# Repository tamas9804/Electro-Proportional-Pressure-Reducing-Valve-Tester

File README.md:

# Elektronikus nyomáscsökkentő szelep tesztelő

## Megvalósítandó funkciók

### 1. Mérési funkciók 
* **Szelepek folytonosságának mérése:** Gyors szakadás- és zárlatvizsgálat a szelepek tekercsén.
* **Nagy pontosságú ellenállásmérés:** A szelepek tekercsellenállásának precíziós mérése **0,1%-os pontossággal**, ami lehetővé teszi a minimális menetzárlatok vagy degradációk kiszűrését is.
* **Többcsatornás architektúra:** A rendszernek alkalmasnak kell lennie egyszerre két szelep fogadására és mérésére/tesztelésére.

### 2. Vezérlési és hajtás funkciók 
* **Teljes kivezérlés:** A szelepek direkt, folyamatos (100%-os) kivezérlése a maximális elmozdulás és működés ellenőrzéséhez.
* **PWM kivezérlés:** Impulzusszélesség-modulált (PWM) jel biztosítása a proporcionális szelepek áram- és nyomásszabályzási karakterisztikájának teszteléséhez.
* **Polaritásváltás (H-híd konfiguráció):** A hardvernek felkészültnek kell lennie a polaritás szoftveres felcserélésére, biztosítva a jövőbeli kompatibilitást a többállású vagy irányváltó szelepekkel.

### 3. Hardver és elektromos védelem 
* **Széles tápfeszültség-tartomány:** Az áramkörnek stabilan kell üzemelnie **12V és 24V DC** közötti betáplálási feszültségen, alkalmazkodva az ipari és járműipari szabványokhoz.
* **Fordított polaritás elleni védelem:** Védelem a tápvezetékek téves felcserélése ellen a belső elektronika megóvása érdekében.
* **Túláramvédelem:** A fő tápágat egy **10A-es biztosíték** védi a zárlatokból vagy túlterhelésekből adódó károk ellen.

### 4. Felhasználói felület és szoftver 
* **Beépített menürendszer:** A műszernek rendelkeznie kell egy lokális kijelzőn és fizikai nyomógombokon keresztül kezelhető, jól strukturált menürendszerrel. A szoftvernek kötelezően biztosítania kell az alábbi dedikált menüpontokat:
  * **Teljes teszt:** Egy automatizált tesztszekvencia, amely felhasználói beavatkozás nélkül, egymás után elvégzi a szakadásvizsgálatot, az ellenállásmérést, és végül teljesen kivezérli a szelepet.
  * **Szakadásvizsgálat:** Külön menüpont a tekercs folytonosságának gyors és célzott ellenőrzésére.
  * **Ellenállásmérés:** Dedikált funkció a szelep tekercsellenállásának precíziós mérésére.
  * **Teljes kivezérlés:** A szelep 100%-os, folyamatos statikus meghajtása az azonnali működés-ellenőrzéshez.
  * **PWM kivezérlés:** Impulzusszélesség-modulált (PWM) jel kiadása a szelep proporcionális mozgásának teszteléséhez.
  * **Beállítások:** Rendszerkonfigurációs menü, ahol a felhasználó megadhatja a tesztelt szelepek számát, illetve kiválaszthatja a kívánt nyelvet.
* **Többnyelvűség:** A szoftver képesnek kell lennie több nyelv (Magyar, Angol, Német) dinamikus kezelésére és tartós tárolására.A műszernek újraindítás után is megkell jegyeznie az elmentett szelepek számát, illetve a beállított nyelvet

##  Kiválasztott hardverkomponensek 

A projekt áramköri kialakítása során a fő szempont a megbízhatóság, a költséghatékonyság, valamint az ipari (12-24V) környezetnek való megfelelés volt. Az áramkör az alábbi főbb alkatrészekre épül:

### 1 Vezérlés és Megjelenítés
* **Arduino Nano (ATmega328P):** Költséghatékony, könnyen programozható, és az I/O lábszáma, valamint a számítási kapacitása tökéletesen elegendő a műszer funkcióinak (állapotgép, I2C kommunikáció, PWM) ellátására.
* **16x4 LCD kijelző (I2C modullal):** A teszteredmények és a menürendszer megjelenítéséért felel. Az I2C bővítőnek köszönhetően mindössze két adatvonalat (SDA, SCL) igényel, így rengeteg portot spórol meg a mikrokontrolleren, és a programozása is rendkívül egyszerű.
### 2 Precíziós Mérésadatgyűjtés
* **ADS1115 (16-bites ADC):** A mikrokontroller beépített, alacsonyabb felbontású analóg-digitális átalakítója helyett ez a dedikált IC garantálja a rendkívül pontos (akár 0,1%-os) áram- és feszültségmérést.
* **LM317 feszültségszabályzó (Áramgenerátoros módban):** A precíziós ellenállásmérés alapja. Stabil, állandó mérőáramot biztosít a szelepek tekercsére, ami elengedhetetlen a pontos ellenállás kiszámításához.
* **Feszültségosztó hálózat:** Egy dedikált, egyszerű és gyors mérőáramkör a tekercsek folytonosságának azonnali ellenőrzésére.
### 3. Teljesítményvezérlés és Tápellátás
* **LM2596S DC-DC Step-down konverter:** A műszer tápegysége. A széles ipari feszültségtartományt (12V - 24V) hatékonyan és biztonságosan alakítja át a logikai áramkörök számára szükséges 5V-os stabil feszültségre.
* **AOD409 (P-csat) és IRLR2705 (N-csat) MOSFET-ek:** Ezek a nagy áramtűrésű tranzisztorok felelnek a szelepek (H-híd topológiájú) meghajtásáért. Biztosítják a biztonságos, melegedésmentes PWM szabályozást és a folyamatos, 100%-os kivezérlést a legnagyobb áramfelvételű szelepek esetén is.
* **SRD-05VDC-SL-C 5V Relék:** Mechanikus kapcsolóelemek, amelyek a különböző mérési körök (pl. áramgenerátoros mérés és PWM hajtás) fizikai és galvanikus leválasztását végzik, védve ezzel az érzékeny mérőelektronikát a tesztelés során.
### 4. Mechanika és Csatlakozók
* **JST XH csatlakozók a PCB-n:** A kijelző, a nyomógombok és a potenciométerek nem közvetlenül a panelre vannak forrasztva, hanem szabványos XH csatlakozókkal csatlakoznak. Ez drasztikusan megkönnyíti az alkatrészek cseréjét, valamint sokkal nagyobb szabadságot ad a végleges műszerház (enclosure) 3D tervezésénél és összeszerelésénél

## Részletes Áramköri Felépítés

Mivel a teljes kapcsolási rajz A3-as méretű, a könnyebb átláthatóság és olvashatóság érdekében funkcionális blokkokra bontva mutatjuk be a hardver működését.

A teljes rajz letölthető [**PDF formátumban**](Hardware/EPPR_tester_full.pdf)

### 1. Tápellátás és Fordított Polaritás Elleni Védelem
Ez a modul felel a rendszer stabil feszültségellátásáért. A 24V-os bemenetet egy biztosíték és egy dióda védi a fordított polaritás ellen. Egy **LM2596S** kapcsolóüzemű szabályzó állítja elő a logikai áramkörök számára szükséges stabil 5V-ot nagy hatásfokkal.

### 2. Vezérlő interfészek és Felhasználói Felület csatlakozók
Itt látható az **Arduino Nano** mikrokontroller központi bekötése. Ez a modul kezeli az I2C buszt az LCD kijelzőt és az ADC-t. Tartalmazza a JST XH csatlakozók bekötését a navigációs nyomógombokhoz, a potméterhez.

#### 3. Precíziós Analóg-Digitális Átalakítás 
A nagy pontosságú mérésekért egy **ADS1115** 16-bites külső ADC modul felel. I2C buszon kommunikál a vezérlővel.

### 4 Polaritás váltó híd 
Ez az áramkör tartalmazza a polaritás váltást az adott kimeneten, illetve kezeli hogy 12V illetve 24V-ről is tudjon működni.

### 5 Mérési Mód Választó Relé 
Ez a modul választja ki, hogy az ADC éppen az analóg mérőjelet vagy a folytonossági teszthez szükséges feszültségosztót olvassa be.

### 6 Szelep Szekvencia Választó Relék
Ez a rész kapcsolja a kimenetet, ezzel a kapcsolással egyszerre két szelep is rácsatlakoztatható és külön külön lemérhető.

### 7 Szelep Csatlakozók és Állapotjelző LED-ek
Ez a kimeneti modul tartalmazza a fizikai sorkapcsokat a szelepek bekötéséhez. Tartalmazza az optikai visszajelzést biztosító LED csatlakozását amelyek mutatják az adott szelep kimenet állapotát.

## Nyomtatott Áramkör 

A megbízható és zajmentes ipari működés érdekében a NYÁK-tervezés során az alábbi tervezési irányelveket követtem:

* **4 rétegű felépítés:** A panel ipari szabványú **FR-4**-es hordozóanyagra készült, 4 rétegű kialakítással. Ez lehetővé tette a jelvezetékek és a tápvezetékek optimális szétválasztását.
* **Dedikált Föld és Táp síkok:** A kiváló zajvédelem érdekében a két belső réteg dedikált feladatot kapott. Az egyik egy megszakítás nélküli, masszív Föld-sík, a másik pedig egy egybefüggő Táp-sík (5V). Ez minimalizálja a hurok-induktivitást és stabil referenciát biztosít a precíziós analóg mérésekhez.
* **Áramra méretezett vezetősávok:** A teljesítményelektronikai részeknél a vezetősávok szélessége a maximális átfolyó áramra lett méretezve a melegedés és a feszültségesés elkerülése végett.
* **Zajszűrés optimalizálása:** A tápszűrő kondenzátorok fizikailag a lehető legközelebb kerültek az integrált áramkörök (Arduino Nano, ADS1115, LM317) táplábaihoz, így hatékonyan nyelik el a magas frekvenciás tranzienseket.
* **Adatvonalak árnyékolása:** A kritikus kommunikációs vonalak (például az I2C busz SDA és SCL vonalai) a rézrétegen mindkét oldalról föld-sávokkal lettek körbevéve. Ez a technika drasztikusan csökkenti az áthallást és megvédi az érzékeny digitális jeleket a relék által keltett zavaroktól.
* **Precíziós Analóg Tápszűrés:** Az **ADS1115** 16-bites ADC tápellátását egy dedikált ferrit szűrővel választottuk le a közös 5V-os digitális tápvezetékről. Ez a szűrőmegoldás hatékonyan blokkolja a mikrokontroller és a digitális kapcsolóelemek által keltett nagyfrekvenciás zajokat, így garantálja a zajmentes tápfeszültséget az ADC számára, ami elengedhetetlen a 0,1%-os mérési pontosság eléréséhez.

## 3D Modell

A nyomtatott áramkörről és a rászerelt alkatrészekről egy teljes 3D modell készült. Ez a modell alapvető fontosságú a műszer külső dobozolásának megtervezéséhez, az ütközések ellenőrzéséhez, valamint a gombok és a kijelző pontos pozicionálásához.

**A PCB 3D-s látványterve :**
[**Kattints ide a panel interaktív 3D megtekintéséhez!**](Hardware/3D%20file/EPPR%20tester.stl)

## Fizikai Összeépítés és Prototípus

Az alábbi képen a már legyártott, 4 rétegű **FR-4**-es nyomtatott áramkör látható a valóságban, készre szerelt állapotban. 

**A kész, működőképes áramkör a valóságban:**

## Szoftver Architektúra és Kódolási Irányelvek 

A beágyazott szoftver **C++ nyelven**, az Arduino keretrendszerre támaszkodva íródott. A kódolás során a fő szempont a megbízhatóság, a mikrokontroller szűkös erőforrásainak optimalizálása, valamint a méréstechnikai pontosság maximalizálása volt.

A fejlesztés során az alábbi kulcsfontosságú programozási technikákat alkalmaztuk:

### 1. Véges Állapotgép 
A szoftver működése egy robusztus, többszintű állapotgépre épül. Az állapotokat (Főmenü, Beállítások, Tesztelési folyamatok) `enum class` struktúrák vezérlik (`SystemMode`, `MenuStates`, `SettingStates`).
* **Előny:** Ez a megközelítés teljesen kiküszöböli az átláthatatlan kódot, és a `loop()` függvényt könnyen bővíthetővé teszi, elkerülve a blokkoló várakozásokat.

### 2. Memóriaoptimalizálás és Többnyelvűség
A műszer három nyelvet támogat (Magyar, Angol, Német). Mivel a kijelzőn megjelenő stringek gyorsan kimerítenék az Arduino Nano (ATmega328P) mindössze 2 kByte-os SRAM memóriáját, az összes szöveges konstans a **Flash memóriában (`PROGMEM`)** kapott helyet.
* **Megvalósítás:** Egy dedikált lekérdező függvény (`getText()`) olvassa ki a kért nyelvi elemeket futásidőben a Flash memóriából egy rövid bufferbe, drasztikusan csökkentve a futásidejű memóriafoglalást.

#### 3. Szoftveres Zajszűrés és Dinamikus Felbontás
A 0,1%-os pontosságú mérés érdekében a hardveres szűrés mellett speciális szoftveres eljárásokat is bevezettem:
* **Túlmintavételezés:** Az analóg értékek beolvasásakor a kód ciklusonként 100 mintát vesz, és ezek átlagolásával (`getAveragedVoltage()`) szűri ki a hálózati és kapcsolási zajokat.
* **Dinamikus Erősítés:** Az ellenállásmérés (`OhmTest`) során a szoftver az ADS1115-ös IC beépített programozható erősítőjét (PGA) dinamikusan állítja (`GAIN_EIGHT`, `GAIN_FOUR`, stb.). Ha a mért feszültség túl alacsony, a rendszer automatikusan nagyobb erősítésre kapcsol, így mindig kihasználja a 16-bites felbontás maximumát a különböző ellenállás-tartományokban.

#### 4. EEPROM Kezelés és "First Start" Detektálás
A felhasználói beállítások (kiválasztott nyelv, szelepek száma) a nem felejtő **EEPROM** memóriában tárolódnak.
* **Intelligens inicializálás:** A szoftver tartalmaz egy `doFirstStart()` logikát, amely egy specifikus azonosító (Magic Number: `78`) keresésével megállapítja, hogy a mikrokontroller most lett-e először felprogramozva. Ha igen, automatikusan feltölti az EEPROM-ot az alapértelmezett gyári értékekkel, megelőzve a memóriaszemétből adódó összeomlásokat.

#### 5. Hardveres Védelem és Tiszta Újraindítás
* A tesztelési fázisok indításakor és leállításakor a szoftver szigorú sorrendben kapcsolja a hardveres reléket és a PWM jeleket, hogy elkerülje a mérőáramkör túlterhelését.
* A beállítások mentése után a rendszer nem szoftveres trükkökkel, hanem a hardveres **Watchdog Timer (`wdt_enable`)** szándékos lejáratásával (`softwareReset()`) hajt végre egy teljesen tiszta újraindítást, garantálva, hogy minden regiszter és memóriacím az alapállapotba kerüljön.

## Javítási és Továbbfejlesztési Tervek 

Bár a műszer prototípusa teljesen működőképes és ellátja az alapvető mérési funkciókat, a jövőbeli verziókhoz az alábbi javítások lehetőségesek:

### Szoftveres javítások és optimalizálás (Known Issues & Fixes)
* **PWM Teszt implementálása:** A menürendszerben már szerepel, de a `PwmTest()` funkció logikája (a hardveres időzítők és a kitöltési tényező dinamikus állítása) még megírásra vár.
* **Blokkoló kódok kiváltása:** A tesztelési folyamatok végén jelenleg `delay(4000)` található. Ezt a jövőben `millis()` alapú, nem blokkoló időzítésre cseréljük, hogy a műszer közben reagálhasson a gombnyomásokra.
* **Kalibrációs menü:** Egy rejtett menüpont létrehozása, ahol az áramgenerátor és a feszültségosztó pontatlanságait szoftveresen (Offset és Gain értékekkel) lehet kalibrálni és az EEPROM-ba menteni.

### Hardveres és Rendszerszintű továbbfejlesztések
* **Induktív visszarúgás elleni védelem:** A jelenlegi V1.0-s nyomtatott áramkörről lemaradtak a szelepek (induktív terhelések) kikapcsolásakor keletkező feszültségtüskék elleni védődiódák. A működő prototípuson ezt ideiglenesen utólagos ráforrasztással oldottuk meg. A következő PCB terv frissítésnél ezek a Schottky védődiódák dedikált helyet és megfelelő hűtőfelületet kapnak a H-híd kimeneteinél, garantálva a MOSFET-ek hosszú távú védelmét.
* **Adatnaplózás (Data Logging):** Egy MicroSD kártya modul integrálása az I2C/SPI buszra, hogy a teszteredményeket .CSV formátumban el lehessen menteni a későbbi elemzéshez.
* **PC-s kommunikáció (Serial Plotter):** A tesztelés alatti áram- és feszültséggörbék (különösen a PWM kivezérlés esetén) folyamatos küldése USB-n keresztül egy PC-s szoftvernek, vizuális grafikonrajzolás céljából.

### Karbantartás és Fizikai javítás 
A hardver úgy lett megtervezve, hogy a terepi javítás a lehető legegyszerűbb legyen:
* **Relék és Csatlakozók:** A mechanikus kopásnak kitett alkatrészek (SRD relék), egy esetleges beégés esetén könnyen kicseréhetővé tétele

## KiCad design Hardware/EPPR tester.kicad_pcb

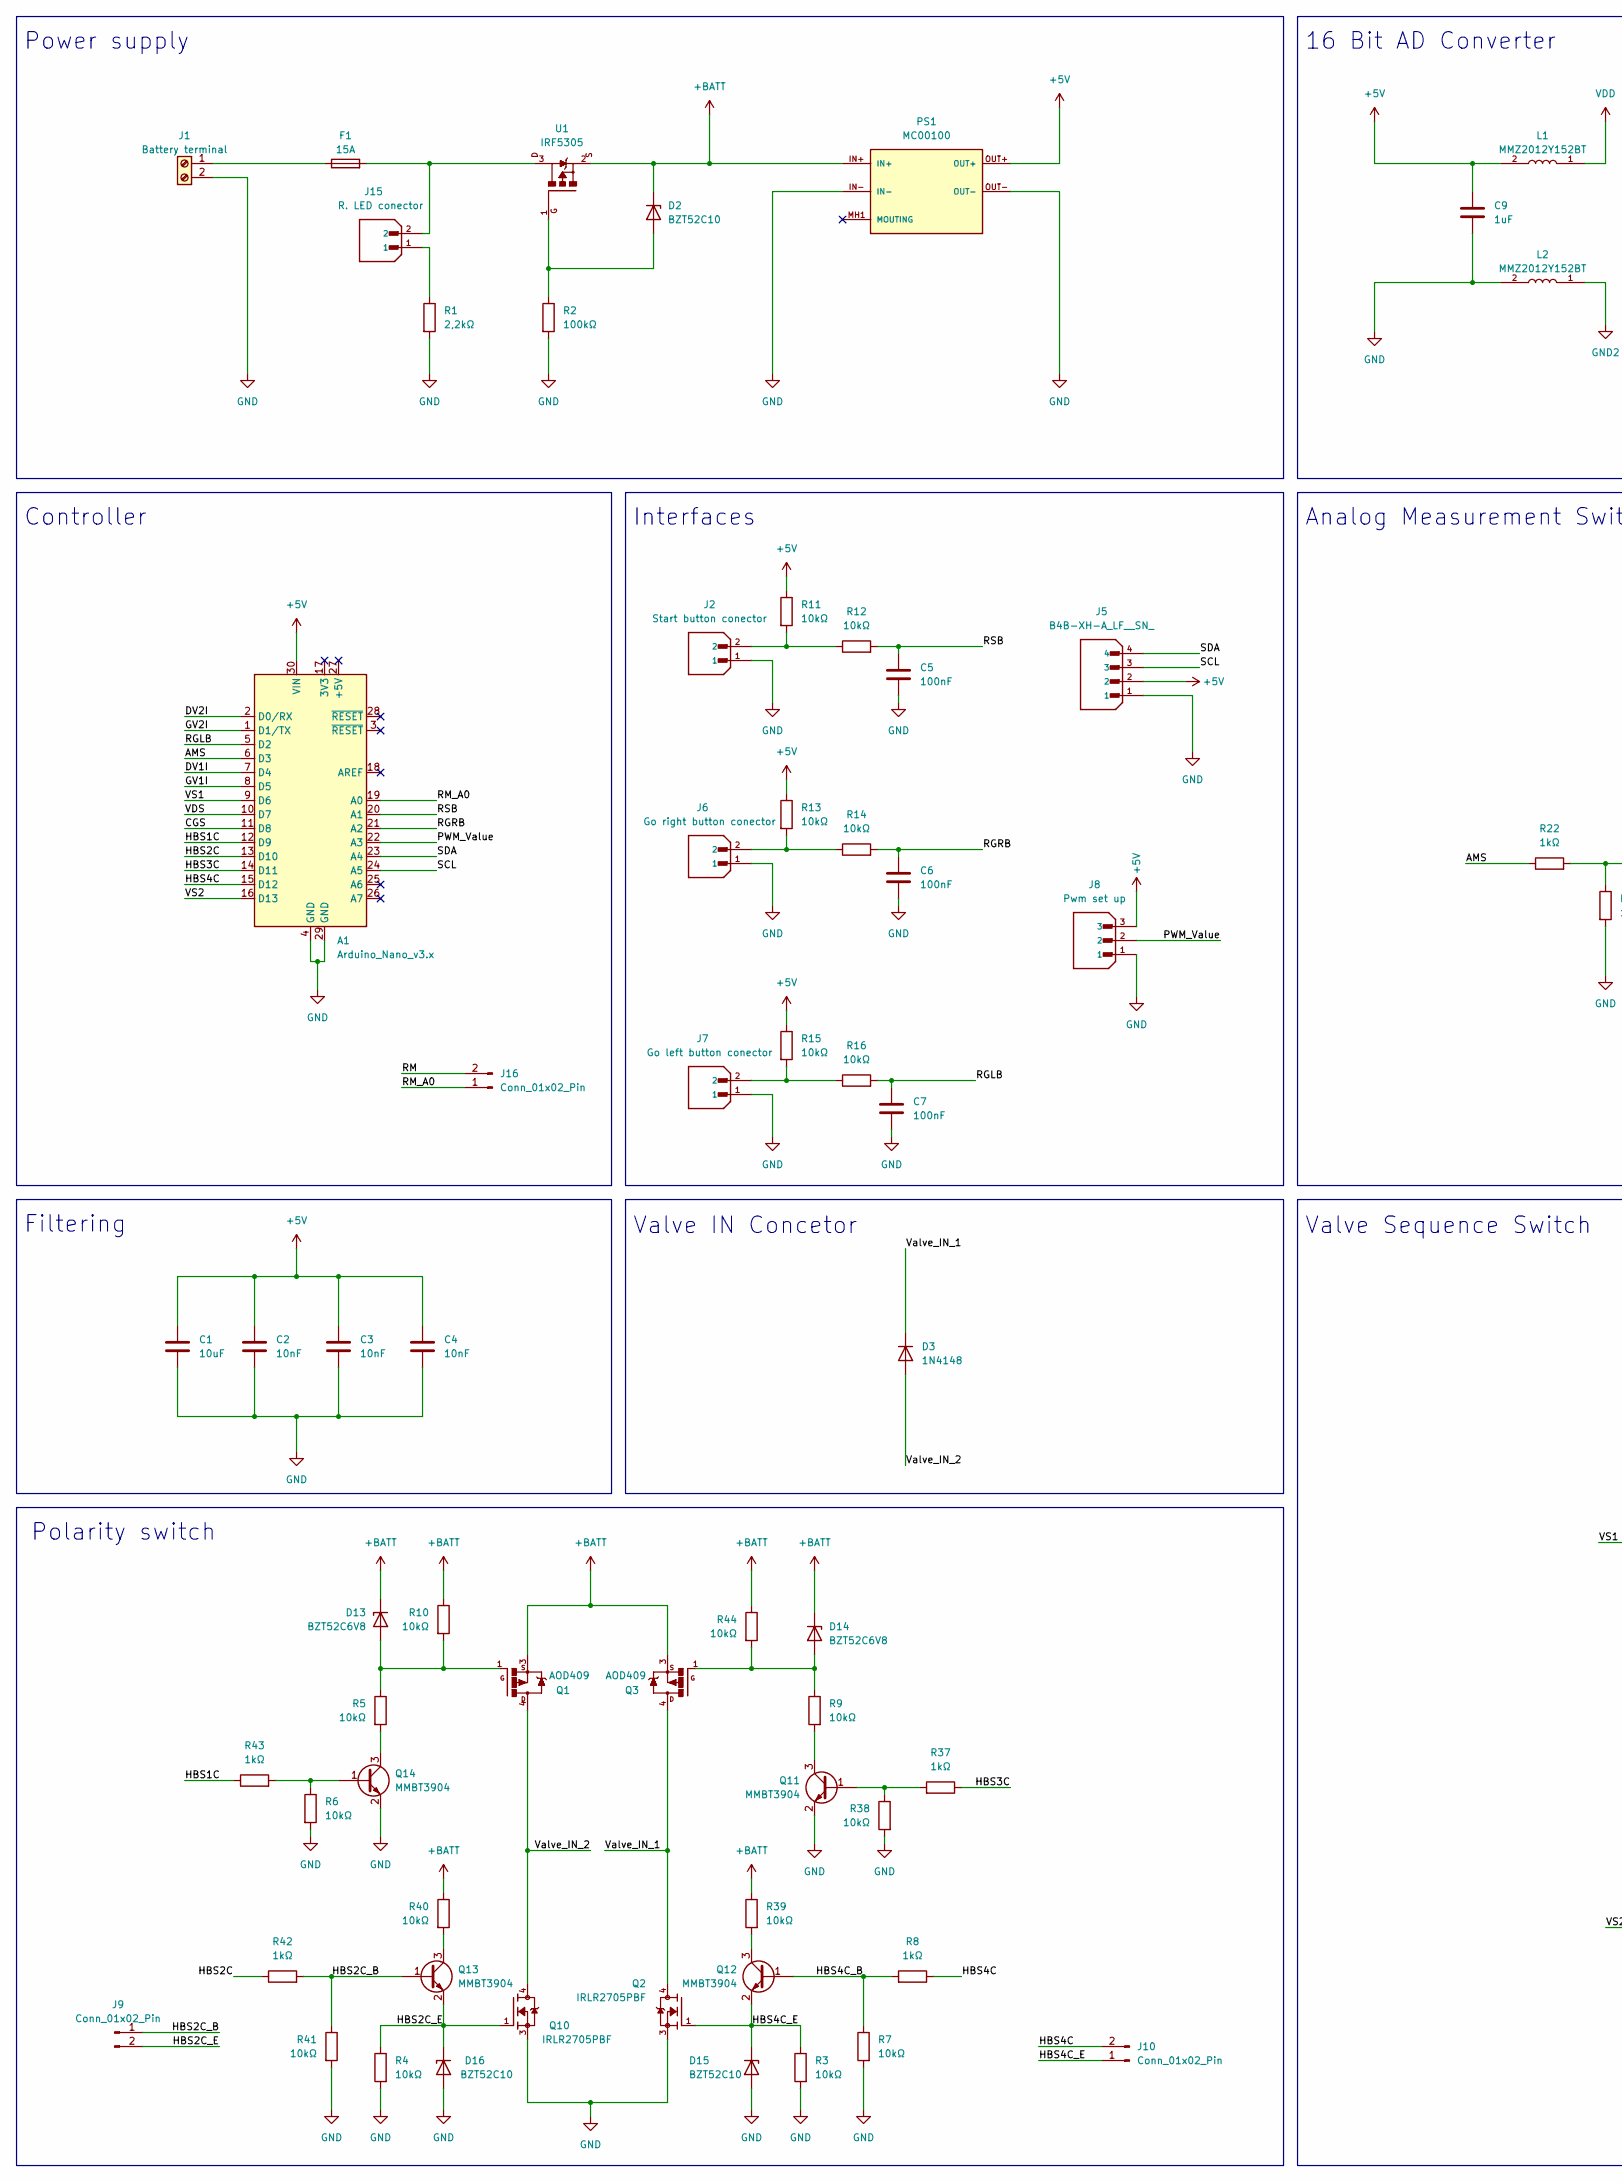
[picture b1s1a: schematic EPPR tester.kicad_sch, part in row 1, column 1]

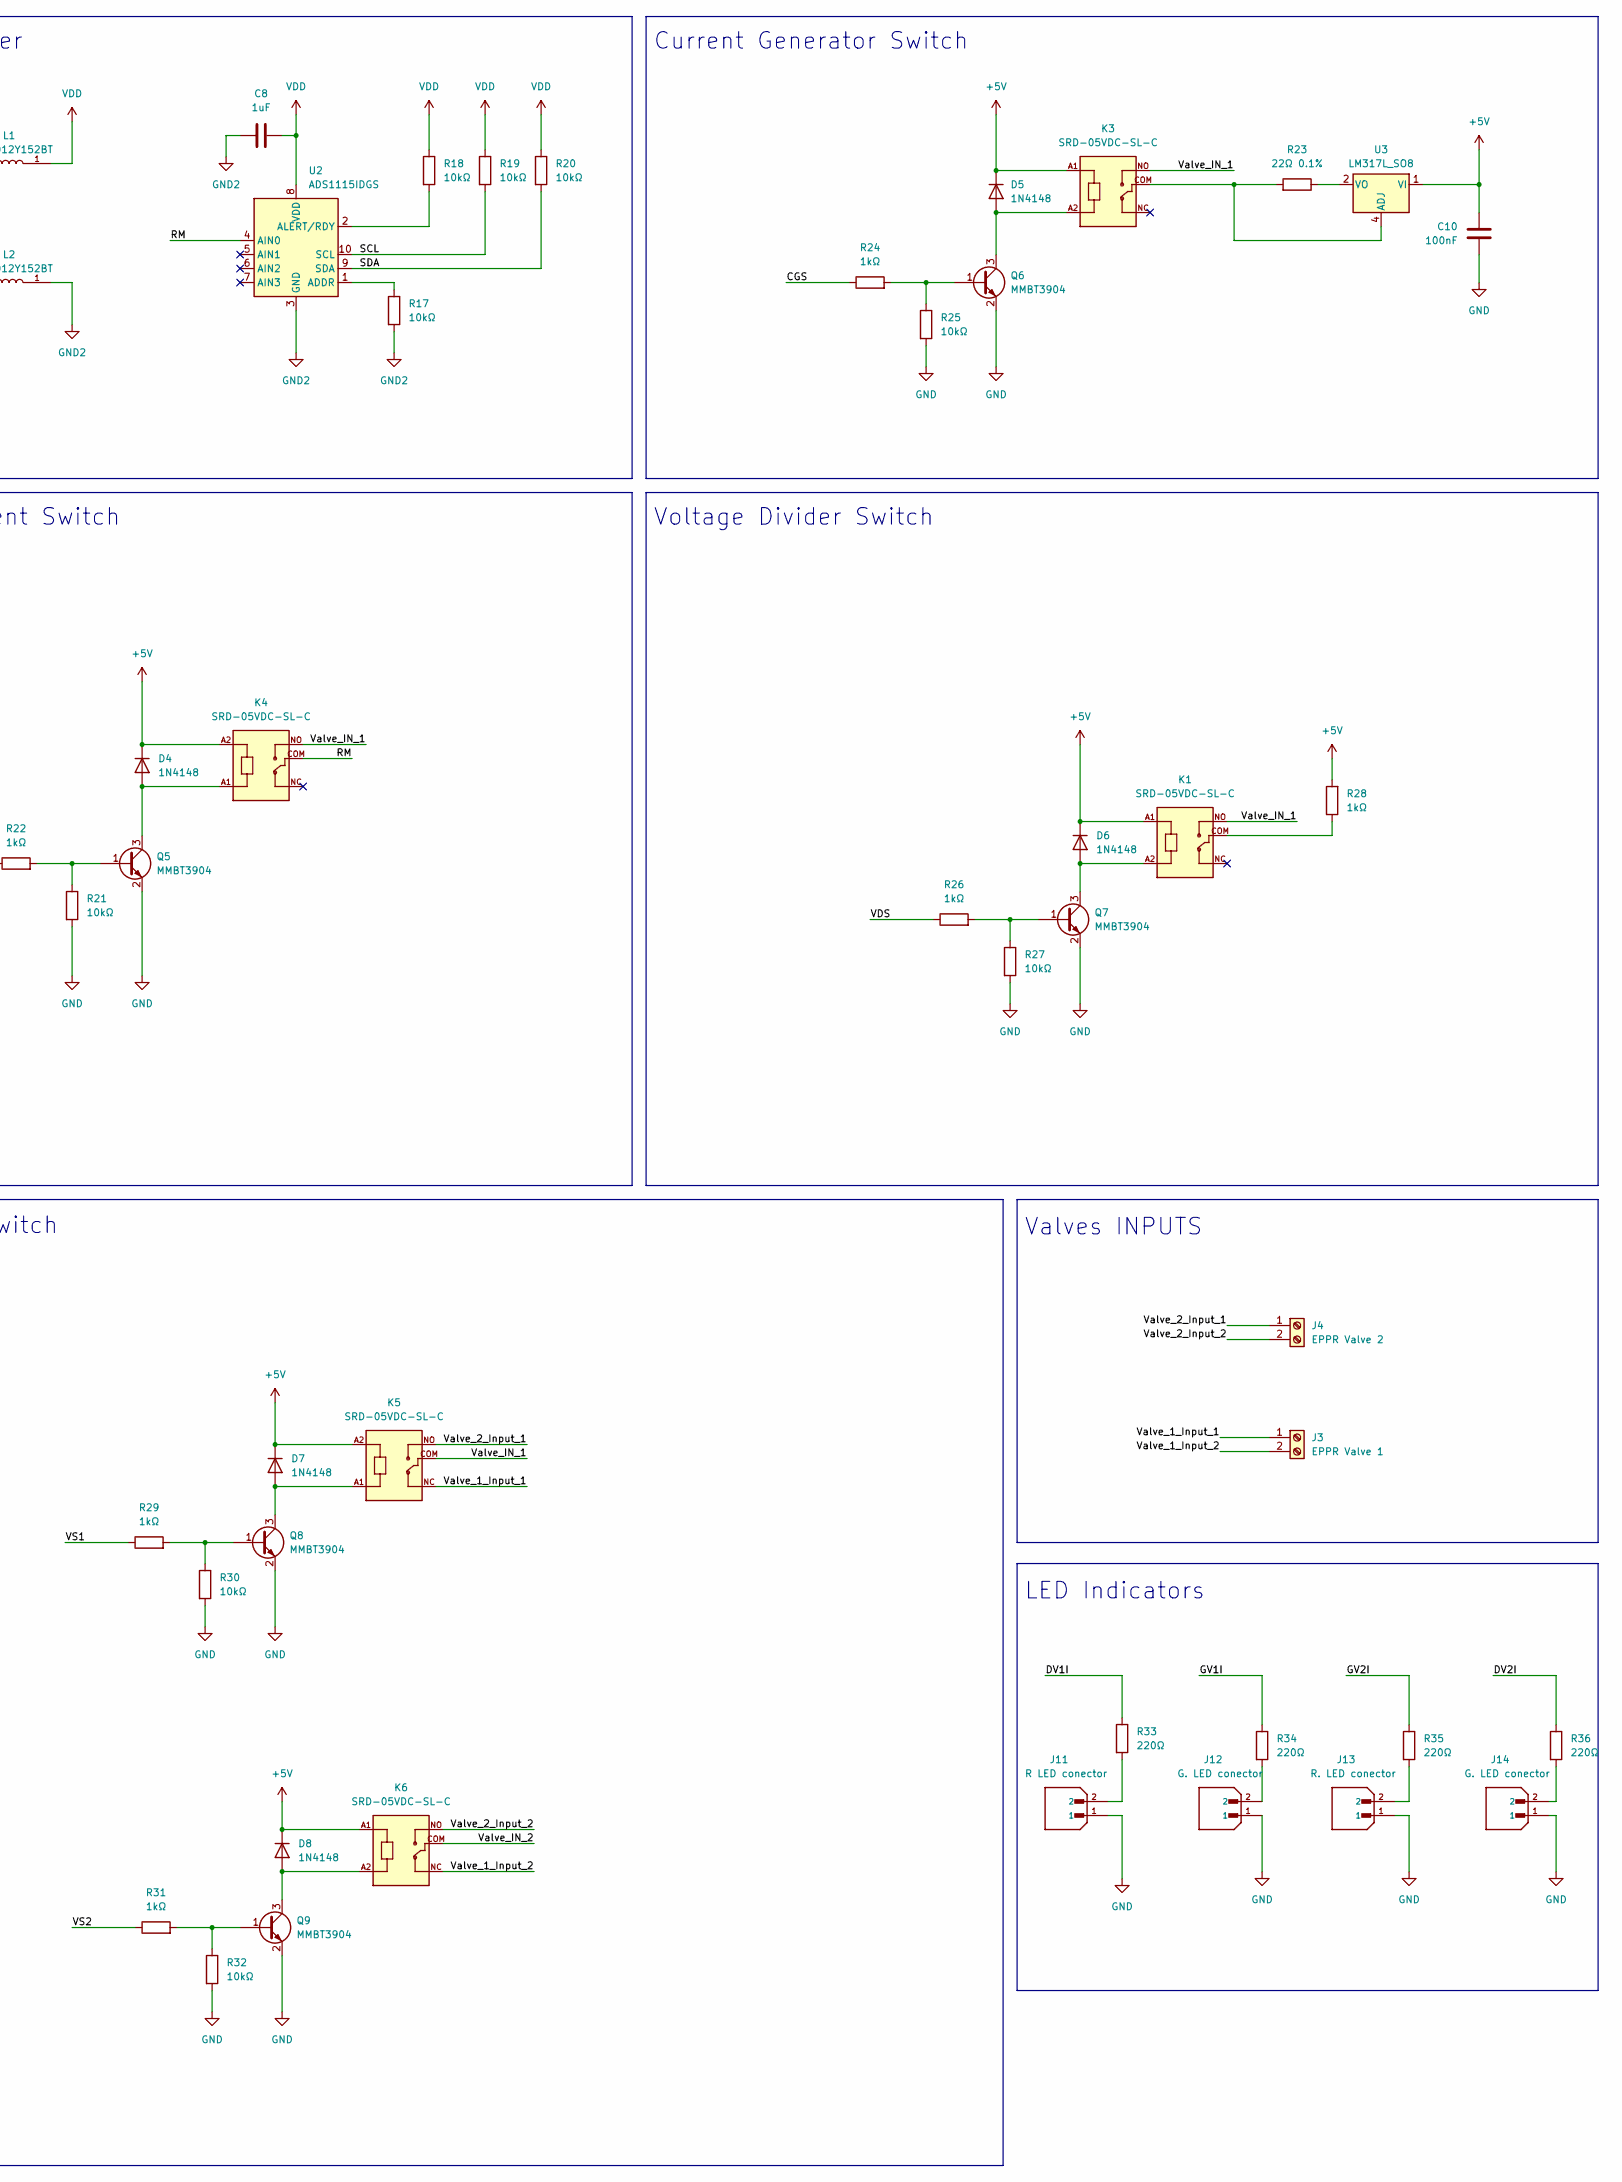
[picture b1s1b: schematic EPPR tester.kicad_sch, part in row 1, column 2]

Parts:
A1: Arduino_Nano_v3.x; Arduino_Nano
C1: 10uF; C_1210_3225Metric_Pad1.33x2.70mm_HandSolder
C2, C3, C4: 10nF; C_0603_1608Metric_Pad1.08x0.95mm_HandSolder
C5, C6, C7, C10: 100nF; C_0603_1608Metric_Pad1.08x0.95mm_HandSolder
C8, C9: 1uF; C_0603_1608Metric_Pad1.08x0.95mm_HandSolder
D2, D15, D16: BZT52C10; Nexperia_CFP3_SOD-123W
D3, D4, D5, D6, D7, D8: 1N4148; D_0603_1608Metric_Pad1.05x0.95mm_HandSolder; Manufacturer_Part_Number CD4148WT(0603C)
D13, D14: BZT52C6V8; Nexperia_CFP3_SOD-123W
F1: 15A; Fuseholder_Littelfuse_100_series_5x20mm
J1: Battery terminal; TerminalBlock_Altech_AK300-2_P5.00mm
J2: Start button conector; JST_B2B-XH-A; PARTREV N/A
J3: EPPR Valve 1; TerminalBlock_Altech_AK300-2_P5.00mm
J4: EPPR Valve 2; TerminalBlock_Altech_AK300-2_P5.00mm
J5: B4B-XH-A_LF__SN_; JST_B4B-XH-A_LF__SN_; PARTREV 7/4/21
J6: Go right button conector; JST_B2B-XH-A; PARTREV N/A
J7: Go left button conector; JST_B2B-XH-A; PARTREV N/A
J8: Pwm set up; JST_B3B-XH-A; PARTREV 7/4/21
J9, J10, J16: Conn_01x02_Pin; R_0402_1005Metric
J11: R LED conector; JST_B2B-XH-A; PARTREV N/A
J12, J14: G. LED conector; JST_B2B-XH-A; PARTREV N/A
J13, J15: R. LED conector; JST_B2B-XH-A; PARTREV N/A
K1, K3, K4, K5, K6: SRD-05VDC-SL-C; RELAY_SRD-05VDC-SL-C
L1, L2: MMZ2012Y152BT; INDC2012X87N
PS1: MC00100; CONV_MC00100; PARTREV NA
Q1, Q3: AOD409; DPAK
Q2, Q10: IRLR2705PBF; TO229P990X239-4N; PARTREV 1/11/05
Q5, Q6, Q7, Q8, Q9, Q11, Q12, Q13, Q14: MMBT3904; SOT-23
R1: 2,2kΩ; R_0603_1608Metric_Pad0.98x0.95mm_HandSolder
R2: 100kΩ; R_0603_1608Metric_Pad0.98x0.95mm_HandSolder
R3, R4, R5, R6, R7, R9, R10, R11, R12, R13, R14, R15, R16, R17, R18, R19, R20, R21, R25, R27, R30, R32, R38, R39, R40, R41, R44: 10kΩ; R_0603_1608Metric_Pad0.98x0.95mm_HandSolder
R8, R22, R24, R26, R28, R29, R31, R37, R42, R43: 1kΩ; R_0603_1608Metric_Pad0.98x0.95mm_HandSolder
R23: 22Ω 0.1%; R_0603_1608Metric_Pad0.98x0.95mm_HandSolder
R33, R34, R35, R36: 220Ω; R_0603_1608Metric_Pad0.98x0.95mm_HandSolder
U1: IRF5305; TO263AB
U2: ADS1115IDGS; TSSOP-10_3x3mm_P0.5mm
U3: LM317L_SO8; SOIC-8_3.9x4.9mm_P1.27mm

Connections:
+5V: A1.30 (VIN), C1.1, C2.1, C3.1, C4.1, C9.2, C10.1, D4.1 (K), D5.1 (K), D6.1 (K), D7.1 (K), D8.1 (K), J5.2, J8.3, K1.A1, K3.A1, K4.A2, K5.A2, K6.A1, L1.2, PS1.OUT+, R11.1, R13.1, R15.1, R28.2, U3.1 (VI)
+BATT: D2.1 (K), D13.1 (K), D14.1 (K), PS1.IN+, Q1.3, Q3.3, R10.1, R39.1, R40.1, R44.1, U1.2
/AMS: A1.6 (D3), R22.1
/CGS: A1.11 (D8), R24.1
/DV1I: A1.7 (D4), R33.1
/DV2I: A1.2 (D0/RX), R36.1
/GV1I: A1.8 (D5), R34.1
/GV2I: A1.1 (D1/TX), R35.1
/HBS1C: A1.12 (D9), R43.1
/HBS2C: A1.13 (D10), R42.1
/HBS2C_B: J9.1, Q13.1 (B), R41.1, R42.2
/HBS2C_E: D16.1 (K), J9.2, Q10.1, Q13.2 (E), R4.1
/HBS3C: A1.14 (D11), R37.1
/HBS4C: A1.15 (D12), J10.2, R8.1
/HBS4C_B: Q12.1 (B), R7.1, R8.2
/HBS4C_E: D15.1 (K), J10.1, Q2.1, Q12.2 (E), R3.1
/PWM_Value: A1.22 (A3), J8.2
/RGLB: A1.5 (D2), C7.1, R16.2
/RGRB: A1.21 (A2), C6.1, R14.2
/RM: J16.2, K4.COM, U2.4 (AIN0)
/RM_A0: A1.19 (A0), J16.1
/RSB: A1.20 (A1), C5.1, R12.2
/SCL: A1.24 (A5), J5.3, R19.2, U2.10 (SCL)
/SDA: A1.23 (A4), J5.4, R20.2, U2.9 (SDA)
/VDS: A1.10 (D7), R26.1
/VS1: A1.9 (D6), R29.1
/VS2: A1.16 (D13), R31.1
/Valve_1_Input_1: J3.1, K5.NC
/Valve_1_Input_2: J3.2, K6.NC
/Valve_2_Input_1: J4.1, K5.NO
/Valve_2_Input_2: J4.2, K6.NO
/Valve_IN_1: D3.1 (K), K1.NO, K3.NO, K4.NO, K5.COM, Q2.4, Q3.4
/Valve_IN_2: D3.2 (A), K6.COM, Q1.4, Q10.4
GND: A1.4 (GND), A1.29 (GND), C1.2, C2.2, C3.2, C4.2, C5.2, C6.2, C7.2, C9.1, C10.2, D15.2 (A), D16.2 (A), J1.2, J2.1, J5.1, J6.1, J7.1, J8.1, J11.1, J12.1, J13.1, J14.1, L2.2, PS1.IN-, PS1.OUT-, Q2.3, Q5.2 (E), Q6.2 (E), Q7.2 (E), Q8.2 (E), Q9.2 (E), Q10.3, Q11.2 (E), Q14.2 (E), R1.2, R2.2, R3.2, R4.2, R6.2, R7.2, R21.2, R25.2, R27.2, R30.2, R32.2, R38.2, R41.2
GND2: C8.1, L2.1, R17.2, U2.3 (GND)
unnamed: D2.2 (A), R2.1, U1.1
unnamed: D4.2 (A), K4.A1, Q5.3 (C)
unnamed: D5.2 (A), K3.A2, Q6.3 (C)
unnamed: D6.2 (A), K1.A2, Q7.3 (C)
unnamed: D7.2 (A), K5.A1, Q8.3 (C)
unnamed: D8.2 (A), K6.A2, Q9.3 (C)
unnamed: D13.2 (A), Q1.1, R5.1, R10.2
unnamed: D14.2 (A), Q3.1, R9.1, R44.2
unnamed: F1.2, J15.2, U1.3
unnamed: F1.1, J1.1
unnamed: J2.2, R11.2, R12.1
unnamed: J6.2, R13.2, R14.1
unnamed: J7.2, R15.2, R16.1
unnamed: J11.2, R33.2
unnamed: J12.2, R34.2
unnamed: J13.2, R35.2
unnamed: J14.2, R36.2
unnamed: J15.1, R1.1
unnamed: K1.COM, R28.1
unnamed: Q5.1 (B), R21.1, R22.2
unnamed: Q6.1 (B), R24.2, R25.1
unnamed: Q7.1 (B), R26.2, R27.1
unnamed: Q8.1 (B), R29.2, R30.1
unnamed: Q9.1 (B), R31.2, R32.1
unnamed: Q11.1 (B), R37.2, R38.1
unnamed: Q11.3 (C), R9.2
unnamed: Q12.3 (C), R39.2
unnamed: Q13.3 (C), R40.2
unnamed: Q14.1 (B), R6.1, R43.2
unnamed: Q14.3 (C), R5.2
unnamed: R23.1, U3.2 (VO), U3.3 (VO), U3.6 (VO), U3.7 (VO)
unnamed: R17.1, U2.1 (ADDR)
unnamed: R18.2, U2.2 (ALERT/RDY)
unnamed: K3.COM, R23.2, U3.4 (ADJ)
VDD: C8.2, L1.1, R18.1, R19.1, R20.1, U2.8 (VDD)

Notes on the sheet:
Interfaces
Voltage Divider Switch
Filtering
LED Indicators
Power supply
Valve IN Concetor
Analog Measurement Switch
Current Generator Switch
16 Bit AD Converter
Polarity switch
Valve Sequence Switch
Controller
Valves INPUTS

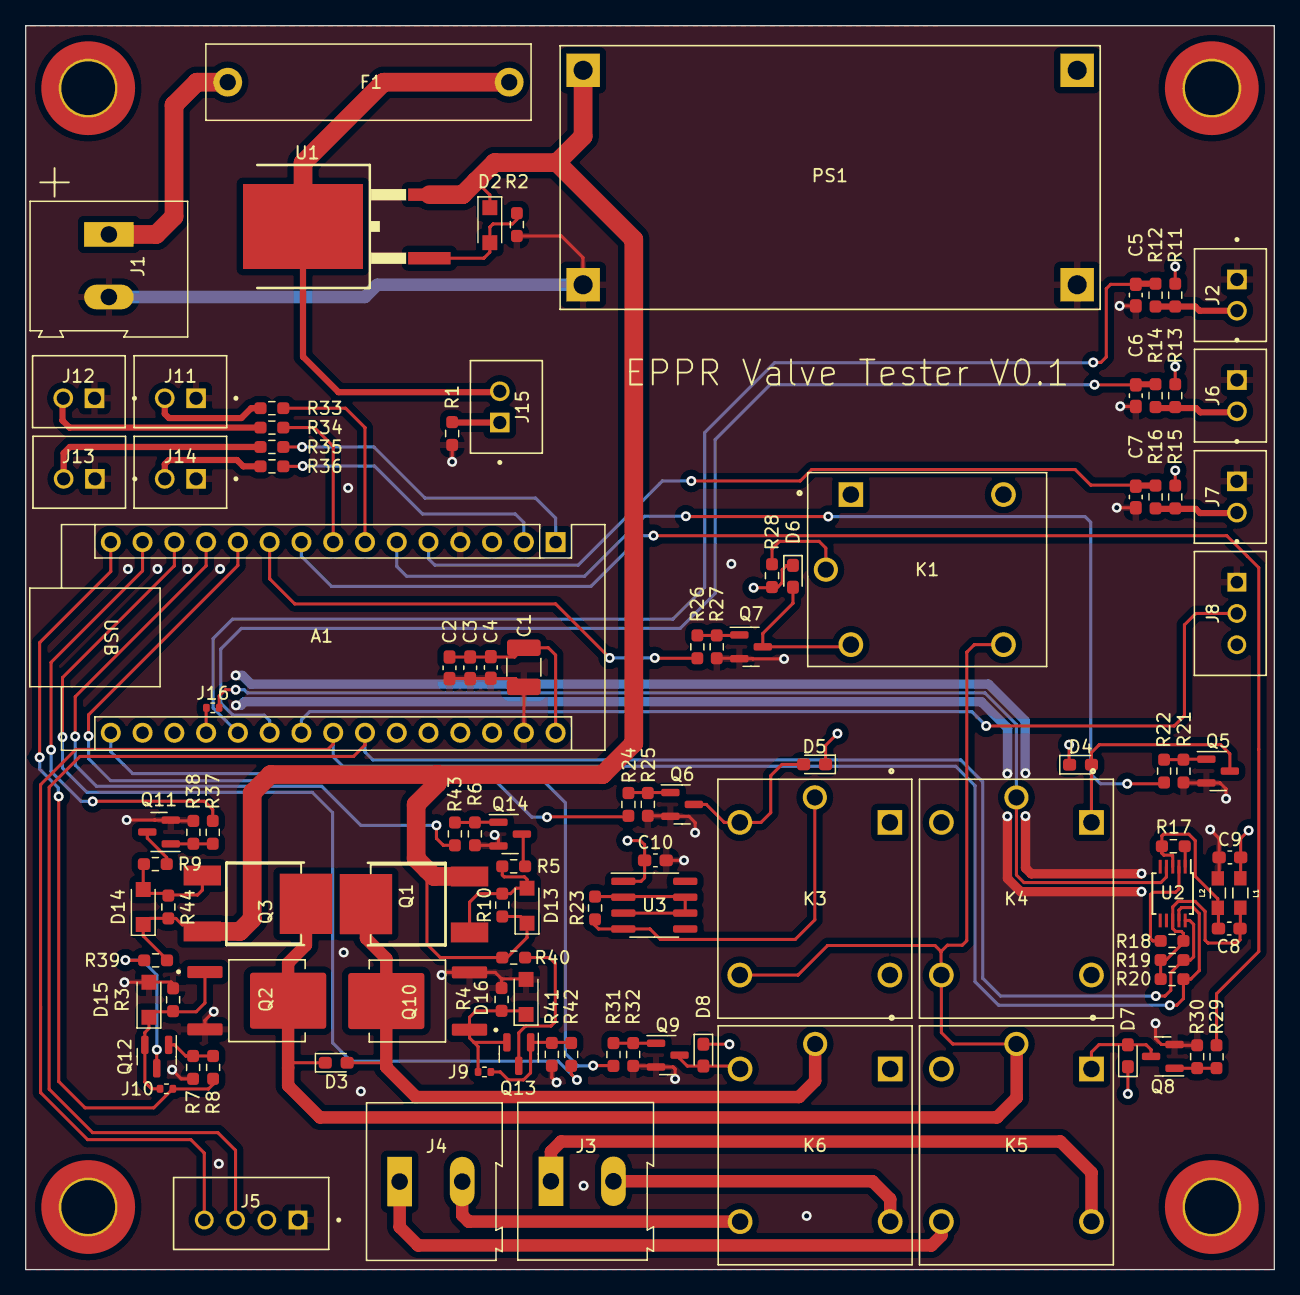
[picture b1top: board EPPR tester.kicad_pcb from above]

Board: 4 copper layers, 99.8 x 99.4 mm, 107 parts (0 on the bottom side), 70 nets.

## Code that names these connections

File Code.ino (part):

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#define ValveSelect1 13
#define ValveSelect2 6

#define HBS1C 9
#define HBS2C 10
#define HBS3C 11
#define HBS4C 12

#define CGS 8
#define VDS 7
#define AMS 3

enum class SystemMode : uint8_t {
  MainMenu,
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  pinMode(ValveSelect1, OUTPUT);
  pinMode(ValveSelect2, OUTPUT);

  pinMode(HBS1C, OUTPUT);
  pinMode(HBS2C, OUTPUT);
  pinMode(HBS3C, OUTPUT);
  pinMode(HBS4C, OUTPUT);

  pinMode(CGS,OUTPUT);
  pinMode(VDS,OUTPUT);
  pinMode(AMS,OUTPUT);

// EZT ki kell majd venni

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
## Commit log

2026-05-23 Add hardware components section to README
    Added hardware components section detailing reliability, cost-effectiveness, and industrial compliance. Included specific components like Arduino Nano, LCD display, ADS1115, and LM317.
2026-05-23 Update section numbering and headings in README
2026-05-23 Fix section header formatting in README.md
2026-05-23 Add schematic and PCB design section to README
    Added section for schematic and PCB design details.
2026-05-23 Fix image link for schematic in README
2026-05-23 Revise README with detailed circuit and power supply info
    Updated the README to include detailed circuit structure and improved clarity on power supply protection.
2026-05-24 Expand README with improvement plans and known issues
    Added future improvement plans and known software issues to the README.
